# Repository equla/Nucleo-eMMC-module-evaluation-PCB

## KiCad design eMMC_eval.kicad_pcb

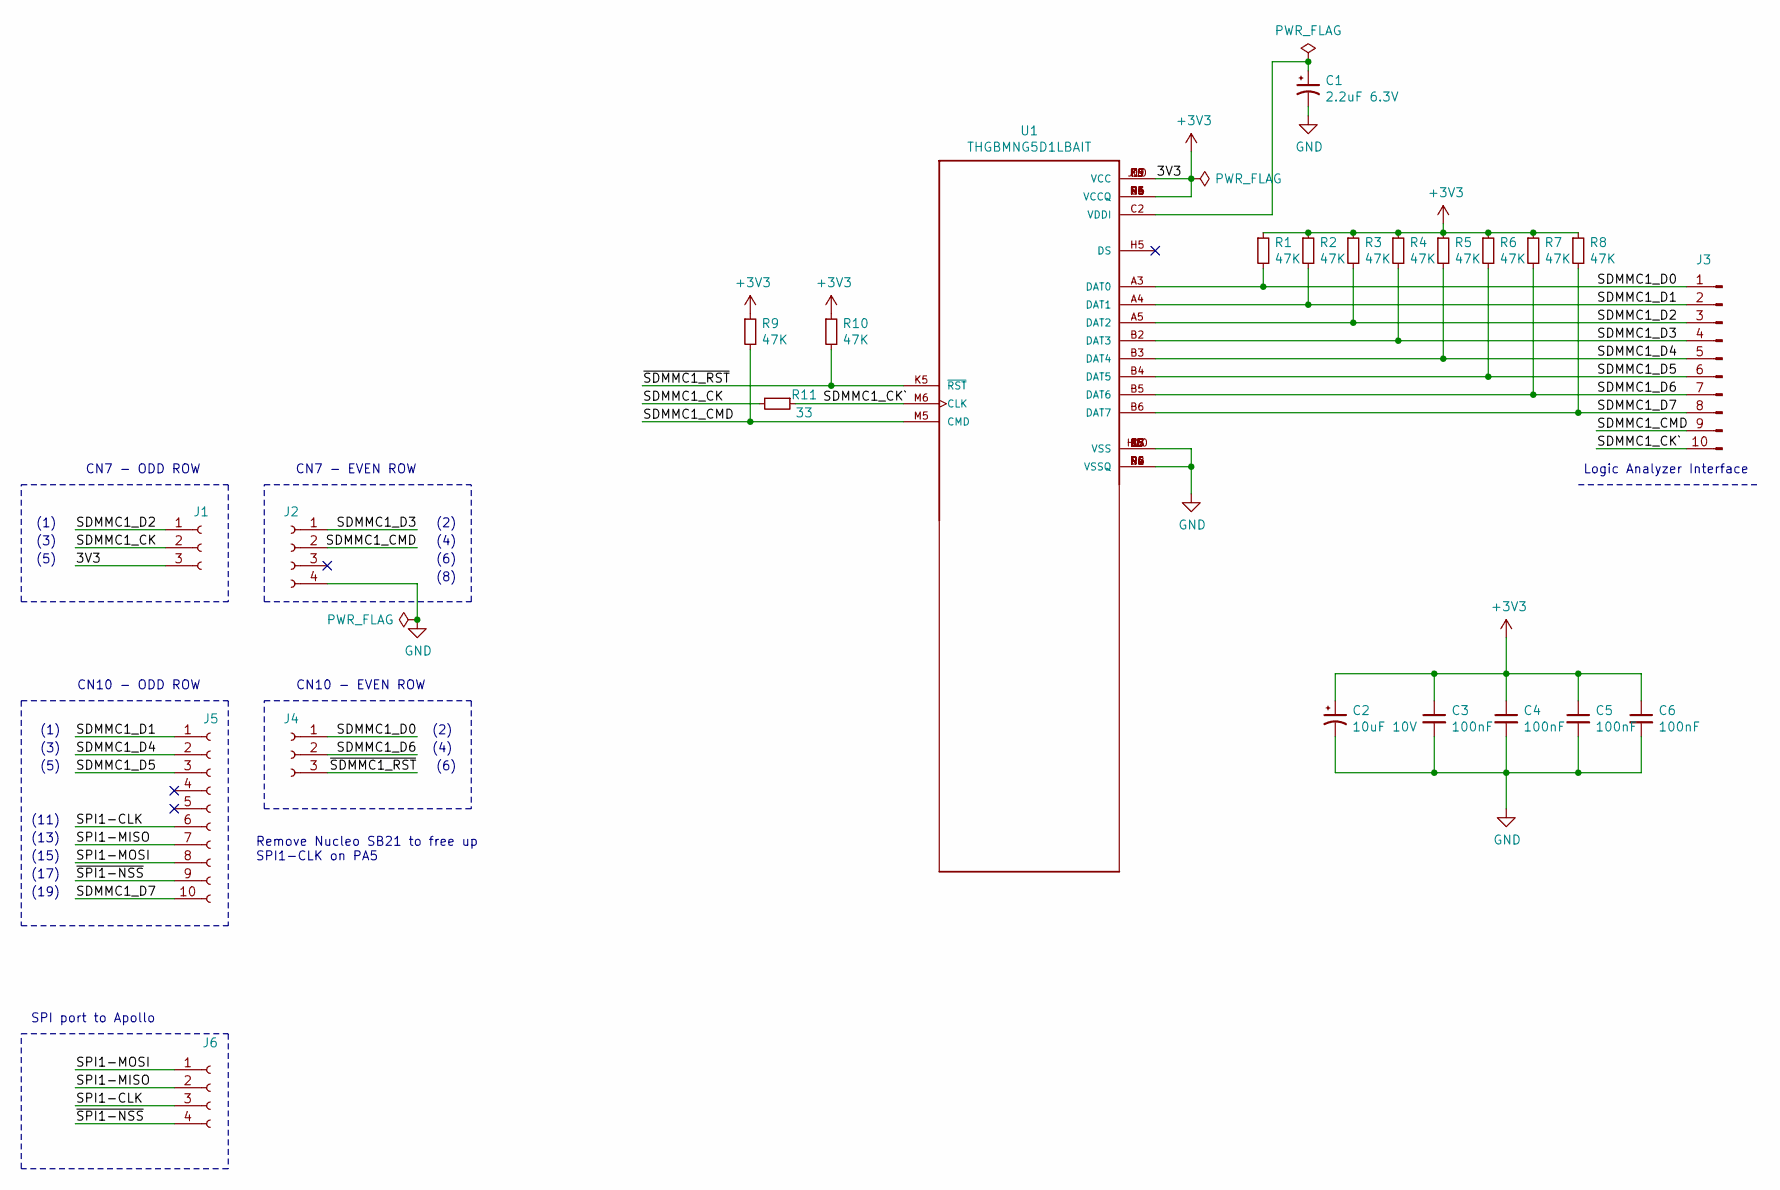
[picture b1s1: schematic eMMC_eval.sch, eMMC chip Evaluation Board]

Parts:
C1: 2.2uF 6.3V; C_0603_1608Metric
C2: 10uF 10V; C_0603_1608Metric
C3, C4, C5, C6: 100nF; C_0603_1608Metric
J1, J4: Conn_01x03_Male; PinSocket_1x03_P2.54mm_Vertical
J2: Conn_01x04_Male; PinSocket_1x04_P2.54mm_Vertical
J3: Conn_01x10_Male; PinHeader_1x10_P2.54mm_Vertical
J5: Conn_01x10_Male; PinSocket_1x10_P2.54mm_Vertical
J6: Conn_01x04_Male; PinHeader_1x04_P2.54mm_Vertical
R1, R2, R3, R4, R5, R6, R7, R8, R9, R10: 47K; R_0805_2012Metric
R11: 33; R_0805_2012Metric
U1: THGBMNG5D1LBAIT; BGA153N50P14X14_1000X1100X80

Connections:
+3V3: C2.1, C3.1, C4.1, C5.1, C6.1, J1.3, R1.1, R2.1, R3.1, R4.1, R5.1, R6.1, R7.1, R8.1, R9.1, R10.1, U1.A9 (VCCQ), U1.B8 (VCCQ), U1.C6 (VCCQ), U1.C7 (VCCQ), U1.E6 (VCC), U1.F5 (VCC), U1.J10 (VCC), U1.K9 (VCC), U1.M4 (VCCQ), U1.N4 (VCCQ), U1.P3 (VCCQ), U1.P5 (VCCQ)
/SDMMC1_CK: J1.2, R11.2
/SDMMC1_CK`: J3.10, R11.1, U1.M6 (CLK), U1.N7 (CLK), U1.P8 (CLK)
/SDMMC1_CMD: J2.2, J3.9, R9.2, U1.L1 (CMD), U1.L2 (CMD), U1.L3 (CMD), U1.M5 (CMD)
/SDMMC1_D0: J3.1, J4.1, R1.2, U1.A3 (DAT0)
/SDMMC1_D1: J3.2, J5.1, R2.2, U1.A4 (DAT1)
/SDMMC1_D2: J1.1, J3.3, R3.2, U1.A5 (DAT2)
/SDMMC1_D3: J2.1, J3.4, R4.2, U1.A1 (DAT3), U1.B2 (DAT3)
/SDMMC1_D4: J3.5, J5.2, R5.2, U1.A2 (DAT4), U1.B3 (DAT4)
/SDMMC1_D5: J3.6, J5.3, R6.2, U1.B4 (DAT5), U1.C3 (DAT5), U1.D2 (DAT5), U1.E1 (DAT5)
/SDMMC1_D6: J3.7, J4.2, R7.2, U1.B5 (DAT6), U1.C5 (DAT6), U1.D4 (DAT6), U1.E3 (DAT6), U1.F2 (DAT6), U1.G1 (DAT6)
/SDMMC1_D7: J3.8, J5.10, R8.2, U1.A8 (DAT7), U1.B6 (DAT7), U1.B7 (DAT7)
/SPI1-CLK: J5.6, J6.3
/SPI1-MISO: J5.7, J6.2
/SPI1-MOSI: J5.8, J6.1
/~SDMMC1_RST: J4.3, R10.2, U1.K5 (~RST~), U1.L12 (~RST), U1.L13 (~RST), U1.L14 (~RST)
/~SPI1-NSS: J5.9, J6.4
GND: C1.2, C2.2, C3.2, C4.2, C5.2, C6.2, J2.4, U1.A6 (VSS), U1.C4 (VSSQ), U1.D3 (VSSQ), U1.E2 (VSSQ), U1.E7 (VSS), U1.F1 (VSSQ), U1.G5 (VSS), U1.H10 (VSS), U1.J5 (VSS), U1.K8 (VSS), U1.N2 (VSSQ), U1.N5 (VSSQ), U1.P1 (VSSQ), U1.P4 (VSSQ), U1.P6 (VSSQ)
unnamed: C1.1, U1.C1 (VDDI), U1.C2 (VDDI)

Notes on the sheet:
CN7 - ODD ROW
CN7 - EVEN ROW
(1)
(3)
(5)
(2)
(4)
(8)
CN10 - ODD ROW
CN10 - EVEN ROW
(19)
Logic Analyzer Interface
(11)
(13)
(15)
Remove Nucleo SB21 to free up SPI1-CLK on PA5
SPI port to Apollo
(6)
(17)

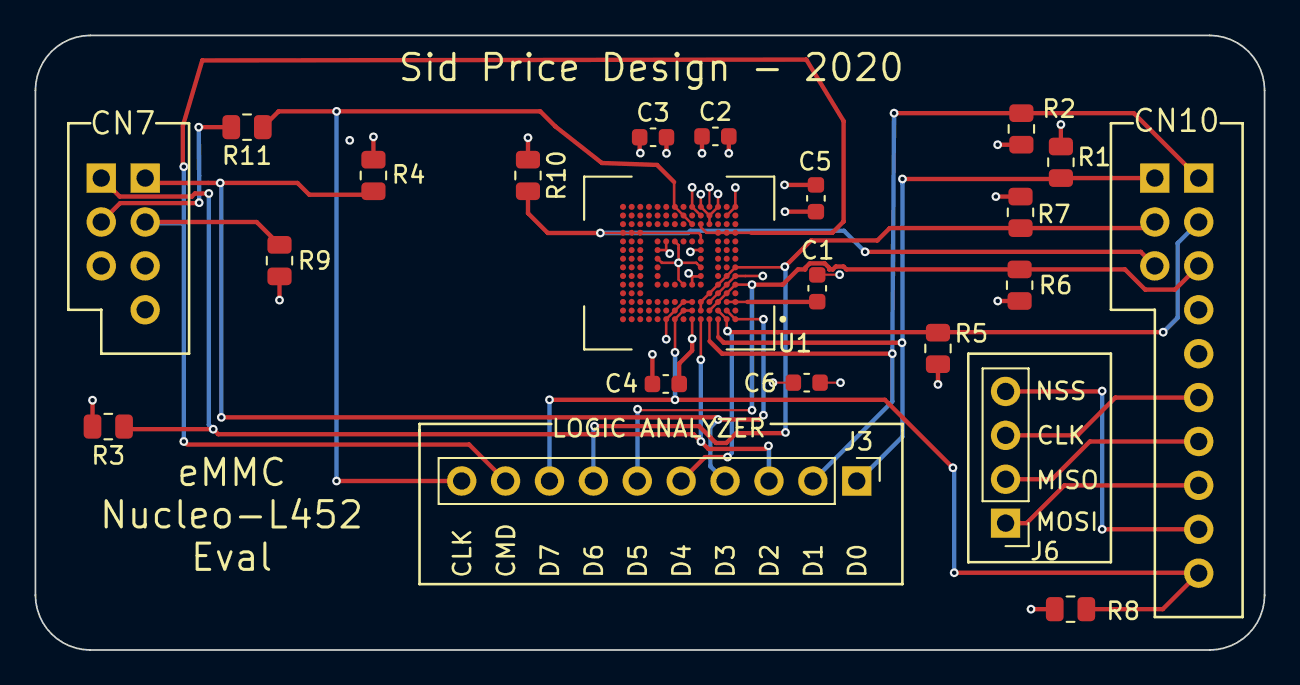
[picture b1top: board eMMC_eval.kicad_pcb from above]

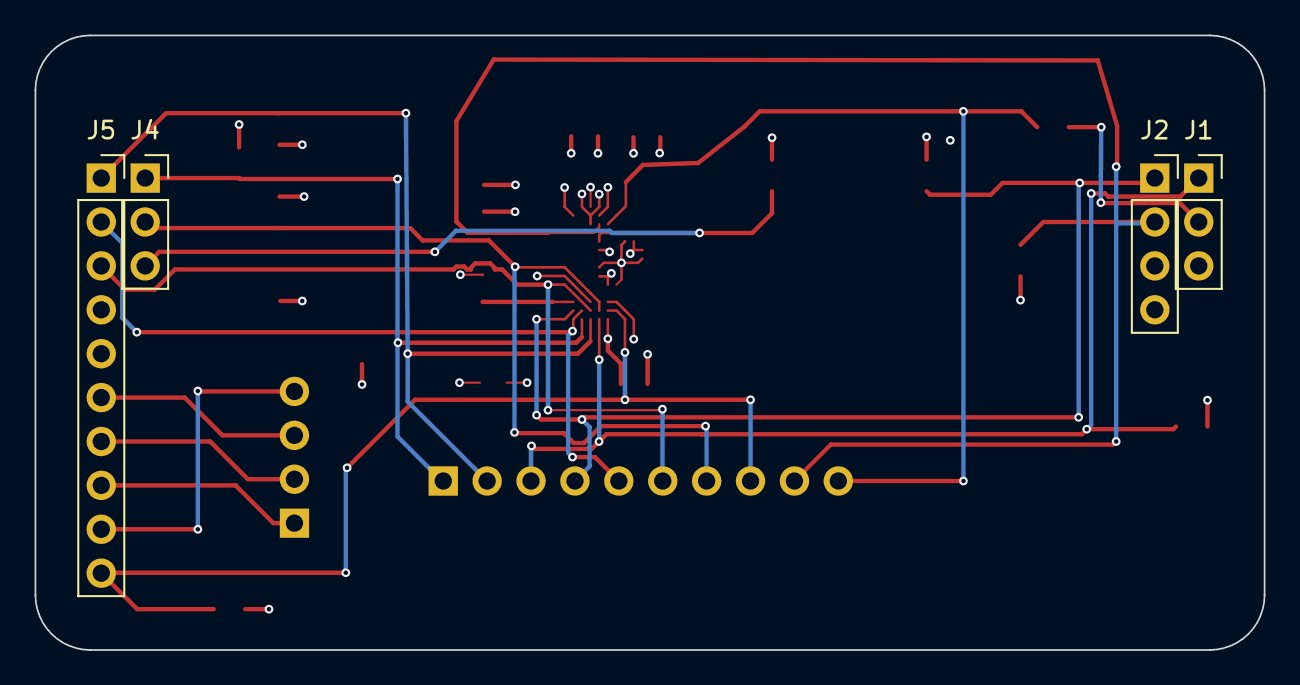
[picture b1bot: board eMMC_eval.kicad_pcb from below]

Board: 4 copper layers, 71.1 x 35.6 mm, 24 parts (4 on the bottom side), 19 nets.

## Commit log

2020-10-05 First revision
    Fabricated at OSHPark
2020-10-07 WIP before back-annotation test
2020-10-07 Back annotate #1
2020-10-07 eMMC chip symbol updated and pushed to PCB
    Has all NC pins remapped to the signals the PCB needs to use to escape the BGA
2020-10-07 Increase track widths where possible
2020-10-07 Fixed SPI header to be pins, added 3D model for eMMC
2020-10-07 Silk Screen adjustments and additions
2020-10-07 Change min track, via, drill to OSHPark specification
2020-11-11 Added pullup resistors and fixed issue with reset input
2020-11-23 Installed and used HtmlBOM
2021-01-28 Value change on CMD pullup
